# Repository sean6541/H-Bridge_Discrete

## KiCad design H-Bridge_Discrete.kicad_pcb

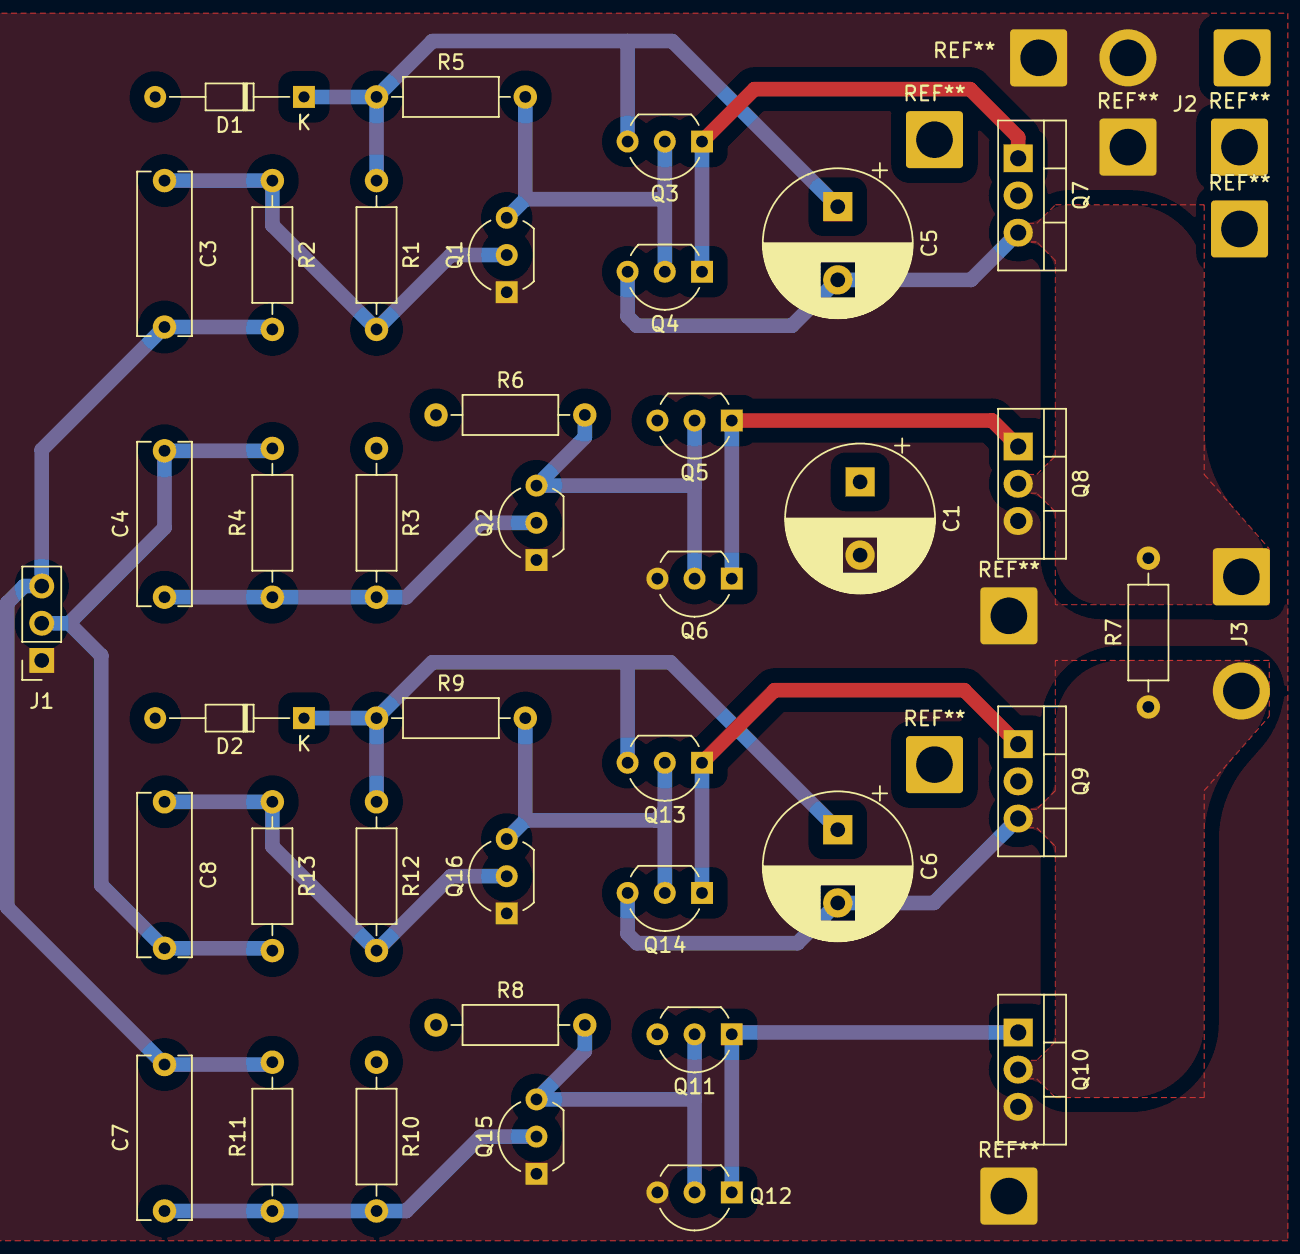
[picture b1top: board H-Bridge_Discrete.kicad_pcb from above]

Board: 2 copper layers, 41 parts (0 on the bottom side), 20 nets.

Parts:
C1: 1000u; CP_Radial_D10.0mm_P5.00mm
C3, C4, C7, C8: 0.1u; C_Rect_L11.0mm_W3.5mm_P10.00mm_MKT
C5, C6: 10u; CP_Radial_D10.0mm_P5.00mm
D1, D2: D; D_DO-34_SOD68_P10.16mm_Horizontal
J1: Conn_01x04; PinSocket_1x03_P2.54mm_Vertical
J2, J3: Screw_Terminal_01x02; SolderWire-2sqmm_1x02_P7.8mm_D2mm_OD3.9mm
Q1, Q2, Q3, Q5, Q11, Q13, Q15, Q16: Q_NPN_EBC; TO-92_Inline_Wide
Q4, Q6, Q12, Q14: Q_PNP_EBC; TO-92_Inline_Wide
Q7, Q8, Q9, Q10: Q_NMOS_GDS; TO-220-3_Vertical
R1, R3, R10, R12: 100k; R_Axial_DIN0207_L6.3mm_D2.5mm_P10.16mm_Horizontal
R2, R4, R11, R13: 2.2k; R_Axial_DIN0207_L6.3mm_D2.5mm_P10.16mm_Horizontal
R5, R6, R8, R9: 1k; R_Axial_DIN0207_L6.3mm_D2.5mm_P10.16mm_Horizontal
R7: 470; R_Axial_DIN0207_L6.3mm_D2.5mm_P10.16mm_Horizontal

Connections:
+12V: C1.1, D1.2, D2.2, J2.1, Q5.3, Q7.2, Q9.2, Q11.3, R3.1, R6.1, R8.1, R10.1
GND: C1.2, J1.1, J2.2, Q1.1, Q2.1, Q6.3, Q8.3, Q10.3, Q12.3, Q15.1, Q16.1
unnamed: C3.1, Q1.2, R1.2, R2.1
unnamed: C4.1, Q2.2, R3.2, R4.1
unnamed: C5.1, D1.1, Q3.3, R1.1, R5.1
unnamed: C6.1, D2.1, Q13.3, R9.1, R12.1
unnamed: C7.1, Q15.2, R10.2, R11.1
unnamed: C8.1, Q16.2, R12.2, R13.1
unnamed: Q1.3, Q3.2, Q4.2, R5.2
unnamed: Q2.3, Q5.2, Q6.2, R6.2
unnamed: Q3.1, Q4.1, Q7.1
unnamed: Q5.1, Q6.1, Q8.1
unnamed: Q10.1, Q11.1, Q12.1
unnamed: Q11.2, Q12.2, Q15.3, R8.2
unnamed: Q9.1, Q13.1, Q14.1
unnamed: Q13.2, Q14.2, Q16.3, R9.2
OUT_A: C5.2, J3.1, Q4.3, Q7.3, Q8.2, R7.2
OUT_B: C6.2, J3.2, Q9.3, Q10.2, Q14.3, R7.1
SIG_A: C3.2, C7.2, J1.3, R2.2, R11.2
SIG_B: C4.2, C8.2, J1.2, R4.2, R13.2
